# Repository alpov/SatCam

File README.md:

# PSAT-2 PSK/SSTV transponder

This repository hosts public parts of two boards from [PSAT2](http://www.aprs.org/psat2.html), a 1.5U CubeSat by US Naval Academy. These boards were developed at Dept. of Radio Electronics, Brno University of Technology, Czech Republic. The source files do not include authorization codes for SSTV and uplink commanding for PSK transponder.

**PSK transponder board** is an updated version of the PSK transponder with beacon and telemetry, used on [PSAT](http://www.aprs.org/psat.html) and [BRICSAT-1](http://www.aprs.org/bricsat-1.html). Transponder documentation available for [PSAT](http://www.urel.feec.vutbr.cz/esl/files/Projects/PSAT/P%20sat%20transponder%20WEB%20spec02.htm) and [BRICSAT-1](http://www.urel.feec.vutbr.cz/esl/files/Projects/BRICsat/Bricsat%20transponder%20WEB%20spec02.htm).

**SSTV transmitter board** provides a Slow-scan Television (SSTV) signal generator with PSK/CW telemetry, APRS uplink, and camera module. It is based on STM32F446RET6 microcontroller. Supported SSTV modes are Robot36, Robot72, MP73 and MP115.

## Important information (UPDATED Aug 2020)

* Current PSAT2 status
  * SSTV 70cm operational, images in Flash occasionally updated (thanks to PY5LF, OK2PNQ, OK5MP)
  * PSK 10m=>70cm transponder operational, mode A, open for users
  * APRS 2m is down (transmitter failure) => user SSTV commanding is not possible

* Please **send your SSTV images** to alpov@alpov.net. I am collecting the emails from reporters and occasionaly send them some news. Other info source is [AMSAT-BB](https://www.amsat.org/pipermail/amsat-bb/).
  * [Gallery of decoded SSTV images](http://www.urel.feec.vutbr.cz/esl/psat2/sstv/).
  * [Online telemetry decoder](http://www.urel.feec.vutbr.cz/esl/psat2/psat2tlm.php) - please use for PSK-31 telemetry upload.
  * [Decoded telemetry of PSK and SSTV boards](https://docs.google.com/spreadsheets/d/1X_4X0AgCshNDFIrDecOif41eRRwNzOKZwRn9tjI5_hs/edit?usp=sharing).
  * [SatNOGS for PSAT2](https://network.satnogs.org/observations/?future=0&good=1&bad=0&unvetted=0&failed=0&norad=44354).

* [Description of overlays](Docs/Overlay.md) in camera images.

* [Standalone camera design](Docs/SatCam.md) (for cancelled [PSAT3](http://www.aprs.org/psat3.html), [operations](Docs/PSAT3-operations.md)).

* [PocketQube camera design](Eagle/satcam_v4B_pocket_pcb_inside.pdf) (for [HADES](https://www.ure.es/camara-sstv-de-la-universidad-de-brno-para-el-satelite-hades-de-amsat-ea/) satellite).

## Transponder modes overview
The main function of the transponder is to receive PSK signals from 29.48 MHz uplink (passband from 29.4804 to 29.4826 MHz) and transmit them as a FM signal at 435.350 MHz downlink. The downlink is mixed with telemetry streams and SSTV images.

The PSK board switches between modes A to D according to available power. Battery voltage is checked periodically and after each transmitted character. If it crosses a boundary, the mode is switched. Moreover, if the voltage falls below a critical limit, the transmission is stopped immediately. This behavior can be observed in mode D, when only a part of the telemetry is transmitted.

All operations are limited to Sun detection, which is controlled by SUNWIRE signal. The SUNWIRE is fail-safe checked by state machine. After MCU reboot, the Sun signal is always high. It goes low after falling edge on SUNWIRE. If the SUNWIRE is low for more than 30 minutes, it is set to high automatically, otherwise with rising edge on SUNWIRE. Interconnects between both boards and PSAT-2 are shown [in a block diagram](Docs/psk_sstv_interconnect.png).

Communication is divided into 20sec time slots. There are 6 slots for modes A/B/C, and 9 slots for mode D. The telemetry is transmitted in every 1st slot or if PSK uplink is detected. Additionally, an SSTV image or telemetry is added to the transmitted signal. The time slots do not affect the PSK transponder function, so there is no need to fit with the PSK uplink signal into a time window. However, advanced functions such as commanding, telemetry and SSTV, are synchronized into these windows.

Users will be able to command these functions after the system has been successfully activated in space and we have completed successful checkout.

## Telemetry streams
The PSK MCU generates telemetry data in PSK31 format, which is transmitted on 435.350 MHz, carrier at 374 Hz. This telemetry consists of current and historical frame. Current frame contains frame counter, reboot counter, values of PSK level, AGC, battery voltage, 5V voltage, current, RX temperature, and several period counter values. History frame is pseudo-randomly selected from memory and contains the same information except for period counters. Example telemetry frame: *PSAT-2 C apng eFaaijtkpokoaB aaaa A aokF eEadjluappjxay*. Such frame can be [decoded with the provided PHP decoder](http://www.urel.feec.vutbr.cz/esl/psat2/psat2tlm.php). Valid telemetry frames are automatically saved for further analysis.

The other telemetry stream is generated by SSTV MCU, transmitted in PSK31 format on the same frequency, carrier at 280 Hz. Telemetry contains current state of non-persistent tick counter, measurements of MCU temperature and ambient light in lux, state of several counters (authorization, planned events, reboots, errors, audio starts, camera images, commands accepted, commands rejected, commands unauthorized). Example telemetry frame: *PSAT-2 S ashd aDbiaaaa qralaitkboFxaa*. Again, such frame can be [decoded with the provided PHP decoder](http://www.urel.feec.vutbr.cz/esl/psat2/psat2tlm.php).

## SSTV operation
SSTV MCU can be commanded through APRS commands. If no command is received during 60 seconds, it starts *auto* mode. In this mode, all transmissions are synchronized to PSK TX. SSTV board can transmit PSK telemetry or SSTV images in Robot36 and MP73 modes. Images are progressively selected alternately from ROM and FLASH. ROM images are hard-coded to firmware, while FLASH images are grabbed from on-board camera. After each reboot, first 8 images in FLASH are taken with 30sec separation.

APRS commands addressed to special callsign will change the mode to *manual*. Details on public commanding will be added after successful deployment and initial testing of the satellite.

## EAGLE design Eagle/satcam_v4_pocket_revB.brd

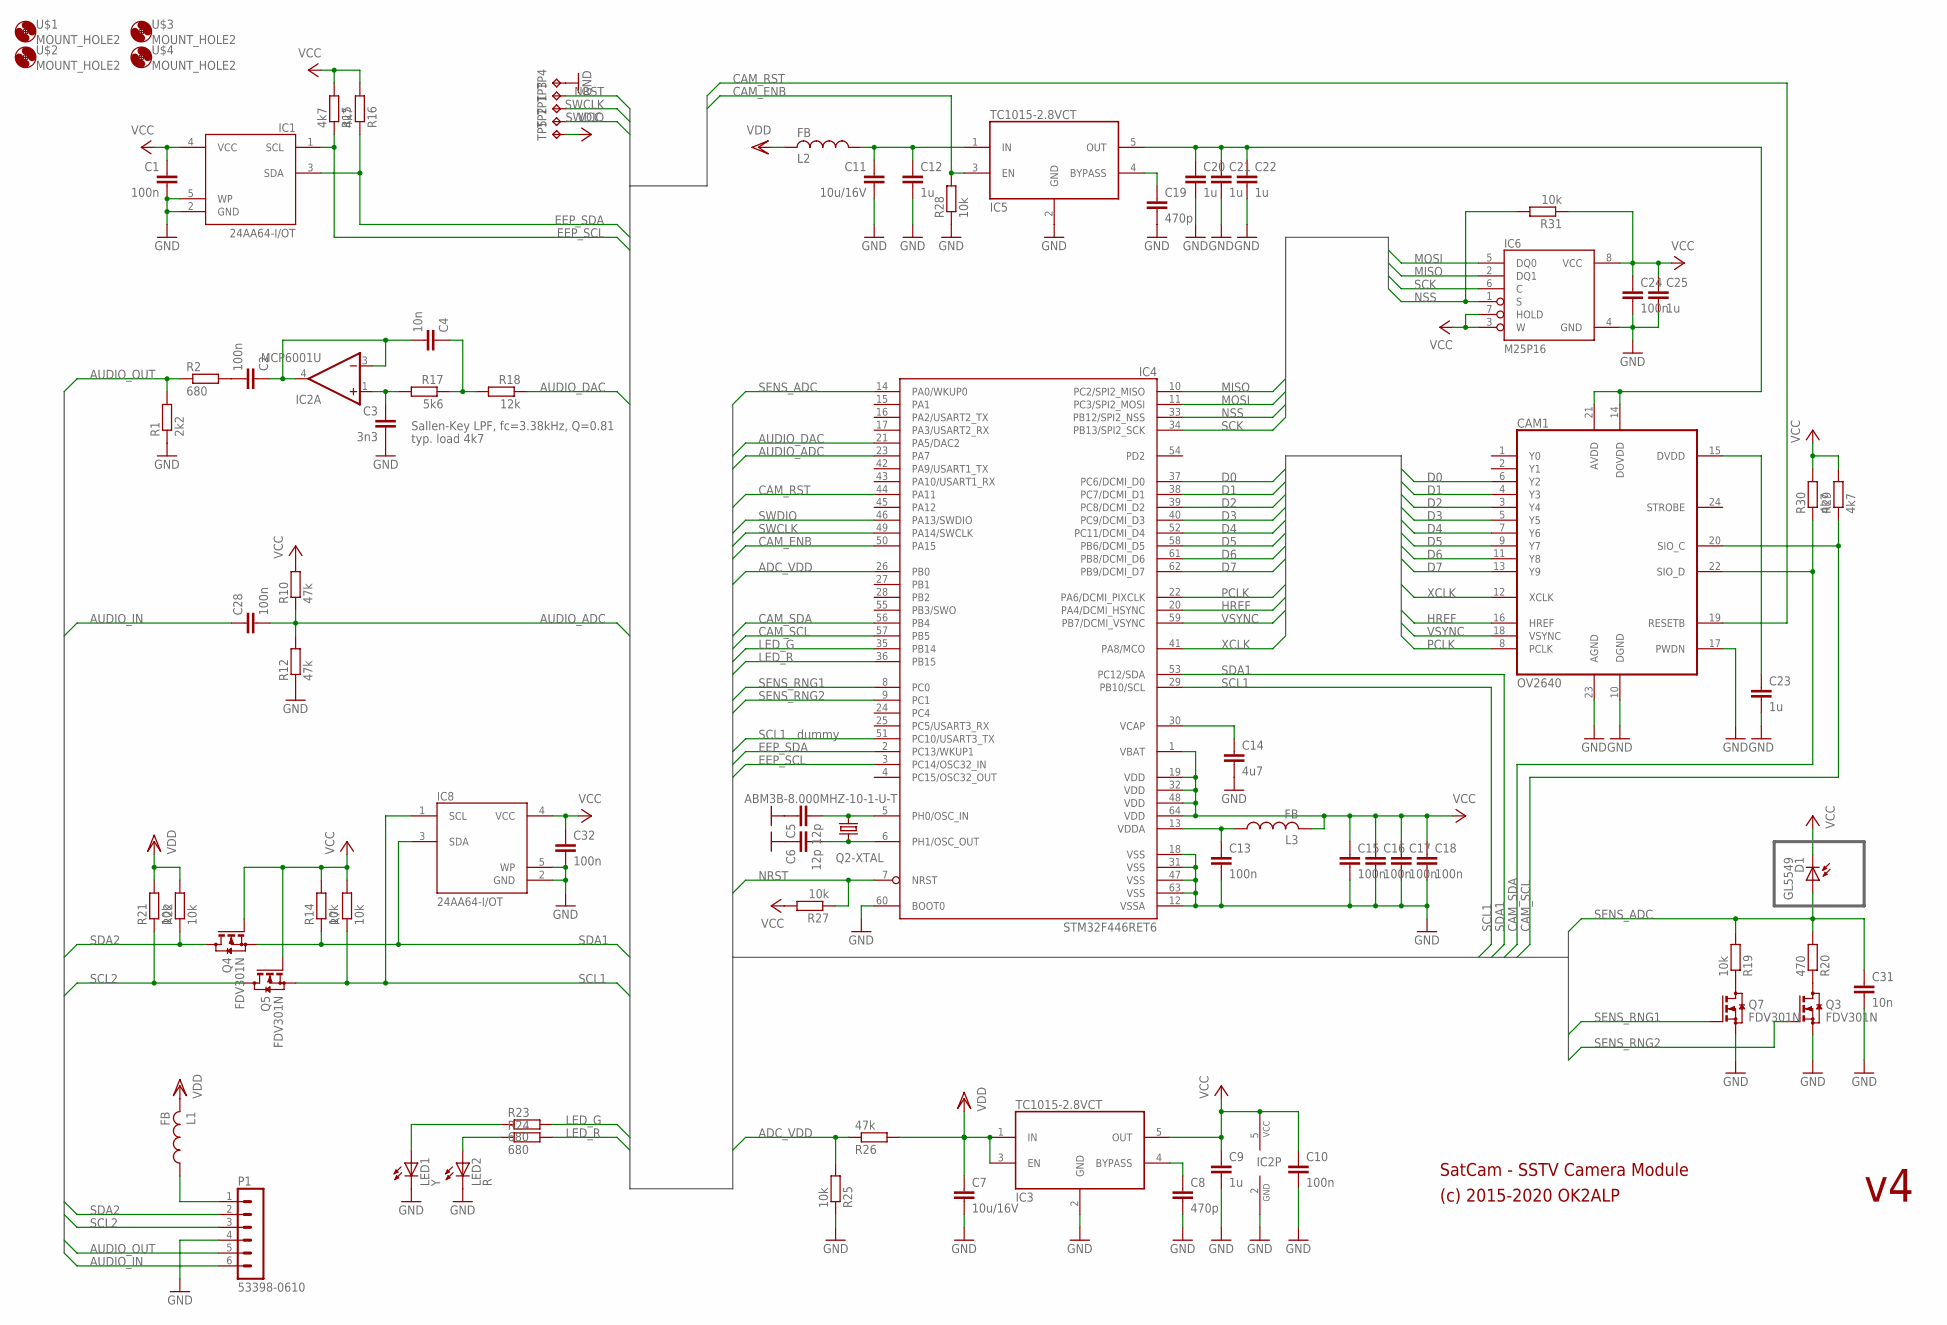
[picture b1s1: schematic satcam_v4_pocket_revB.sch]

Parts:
C1, C2, C10, C13, C15, C16, C17, C18, C24, C28, C32: 100n; C0603
C3: 3n3; C0603
C4, C31: 10n; C0603
C5, C6: 12p; C0603
C7, C11: 10u/16V; C0805K
C8, C19: 470p; C0603
C9, C12, C20, C25: 1u; C0603
C14: 4u7; C0603
C21, C22, C23: 1u; C0402
CAM1: OV2640; 52745-2490
D1: GL5549; LED3MM
IC1, IC8: 24AA64-I/OT; SOT23-5
IC2: MCP6001U; SOT23-5
IC3, IC5: TC1015-2.8VCT; SOT23-5
IC4: STM32F446RET6; TQFP64-10X10
IC6: M25P16; SO08
L1, L2, L3: FB; R0603
LED1: Y; CHIP-LED0603
LED2: R; CHIP-LED0603
P1: 53398-0610
Q2: ABM3B-8.000MHZ-10-1-U-T; CER5032
Q3, Q4, Q5, Q7: FDV301N; SOT23
R1: 2k2; R0603
R2, R23, R24: 680; R0603
R7, R14, R19, R21, R22, R25, R27, R28, R31: 10k; R0603
R10, R12, R26: 47k; R0603
R15, R16, R29, R30: 4k7; R0603
R17: 5k6; R0603
R18: 12k; R0603
R20: 470; R0603
TP1, TP2, TP3, TP4, TP5: TPB1,27; B1,27
U$1, U$2, U$3, U$4: MOUNT_HOLE2; 3,2

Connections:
ADC_VDD: IC4.26 (PB0), R25.2, R26.1
AUDIO_ADC: C28.2, IC4.23 (PA7), R10.1, R12.2
AUDIO_DAC: IC4.21 (PA5/DAC2), R18.1
AUDIO_IN: C28.1, P1.6
AUDIO_OUT: P1.5, R1.2, R2.1
CAM_ENB: IC4.50 (PA15), IC5.3 (EN), R28.2
CAM_RST: CAM1.19 (RESETB), IC4.44 (PA11)
CAM_SCL: CAM1.20 (SIO_C), IC4.57 (PB5), R29.1
CAM_SDA: CAM1.22 (SIO_D), IC4.56 (PB4), R30.1
D0: CAM1.6 (Y2), IC4.37 (PC6/DCMI_D0)
D1: CAM1.4 (Y3), IC4.38 (PC7/DCMI_D1)
D2: CAM1.3 (Y4), IC4.39 (PC8/DCMI_D2)
D3: CAM1.5 (Y5), IC4.40 (PC9/DCMI_D3)
D4: CAM1.7 (Y6), IC4.52 (PC11/DCMI_D4)
D5: CAM1.9 (Y7), IC4.58 (PB6/DCMI_D5)
D6: CAM1.11 (Y8), IC4.61 (PB8/DCMI_D6)
D7: CAM1.13 (Y9), IC4.62 (PB9/DCMI_D7)
EEP_SCL: IC1.1 (SCL), IC4.3 (PC14/OSC32_IN), R15.1
EEP_SDA: IC1.3 (SDA), IC4.2 (PC13/WKUP1), R16.1
GND: C1.2, C3.2, C5.1, C6.1, C7.2, C8.2, C9.2, C10.2, C11.2, C12.2, C13.2, C14.2, C15.2, C16.2, C17.2, C18.2, C19.2, C20.2, C21.2, C22.2, C23.2, C24.2, C25.2, C31.2, C32.2, CAM1.10 (DGND), CAM1.17 (PWDN), CAM1.23 (AGND), IC1.2 (GND), IC1.5 (WP), IC2.2 (GND), IC3.2 (GND), IC4.12 (VSSA), IC4.18 (VSS), IC4.31 (VSS), IC4.47 (VSS), IC4.60 (BOOT0), IC4.63 (VSS), IC5.2 (GND), IC6.4 (GND), IC8.2 (GND), IC8.5 (WP), LED1.C, LED2.C, P1.4, Q2.2 (GND), Q2.4 (GND), Q3.2 (S), Q7.2 (S), R1.1, R12.1, R25.1, R28.1, TP4.TP
HREF: CAM1.16 (HREF), IC4.20 (PA4/DCMI_HSYNC)
LED_G: IC4.35 (PB14), R23.2
LED_R: IC4.36 (PB15), R24.2
MISO: IC4.10 (PC2/SPI2_MISO), IC6.2 (DQ1)
MOSI: IC4.11 (PC3/SPI2_MOSI), IC6.5 (DQ0)
unnamed: C11.1, C12.1, IC5.1 (IN), L2.1
unnamed: C23.1, CAM1.15 (DVDD)
unnamed: C19.1, IC5.4 (BYPASS)
unnamed: L1.1, P1.1
unnamed: C8.1, IC3.4 (BYPASS)
unnamed: LED2.A, R24.1
unnamed: LED1.A, R23.1
unnamed: C14.1, IC4.30 (VCAP)
unnamed: Q7.3 (D), R19.1
unnamed: Q3.3 (D), R20.1
unnamed: C13.1, IC4.13 (VDDA), L3.1
unnamed: C6.2, IC4.6 (PH1/OSC_OUT), Q2.3 (2)
unnamed: C5.2, IC4.5 (PH0/OSC_IN), Q2.1
unnamed: C2.1, C4.2, IC2.3 (-IN), IC2.4 (OUT)
unnamed: C4.1, R17.1, R18.2
unnamed: C3.1, IC2.1 (+IN), R17.2
unnamed: C2.2, R2.2
NRST: IC4.7 (NRST), R27.1, TP3.TP
NSS: IC4.33 (PB12/SPI2_NSS), IC6.1 (S), R31.2
PCLK: CAM1.8 (PCLK), IC4.22 (PA6/DCMI_PIXCLK)
SCK: IC4.34 (PB13/SPI2_SCK), IC6.6 (C)
SCL1: IC4.29 (PB10/SCL), IC4.51 (PC10/USART3_TX), IC8.1 (SCL), Q5.2 (S), R7.1
SCL2: P1.3, Q5.3 (D), R21.1
SDA1: IC4.53 (PC12/SDA), IC8.3 (SDA), Q4.2 (S), R14.1
SDA2: P1.2, Q4.3 (D), R22.1
SENS_ADC: C31.1, D1.A, IC4.14 (PA0/WKUP0), R19.2, R20.2
SENS_RNG1: IC4.8 (PC0), Q7.1 (G)
SENS_RNG2: IC4.9 (PC1), Q3.1 (G)
SWCLK: IC4.49 (PA14/SWCLK), TP1.TP
SWDIO: IC4.46 (PA13/SWDIO), TP2.TP
VCAM: C20.1, C21.1, C22.1, CAM1.14 (DOVDD), CAM1.21 (AVDD), IC5.5 (OUT)
VCC: C1.1, C9.1, C10.1, C15.1, C16.1, C17.1, C18.1, C24.1, C25.1, C32.1, D1.K (C), IC1.4 (VCC), IC2.5 (VCC), IC3.5 (OUT), IC4.1 (VBAT), IC4.19 (VDD), IC4.32 (VDD), IC4.48 (VDD), IC4.64 (VDD), IC6.3 (W), IC6.7 (HOLD), IC6.8 (VCC), IC8.4 (VCC), L3.2, Q4.1 (G), Q5.1 (G), R7.2, R10.2, R14.2, R15.2, R16.2, R27.2, R29.2, R30.2, R31.1, TP5.TP
VDD: C7.1, IC3.1 (IN), IC3.3 (EN), L1.2, L2.2, R21.2, R22.2, R26.2
VSYNC: CAM1.18 (VSYNC), IC4.59 (PB7/DCMI_VSYNC)
XCLK: CAM1.12 (XCLK), IC4.41 (PA8/MCO)

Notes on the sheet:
typ. load 4k7
Sallen-Key LPF, fc=3.38kHz, Q=0.81
SatCam - SSTV Camera Module
(c) 2015-2020 OK2ALP
dummy

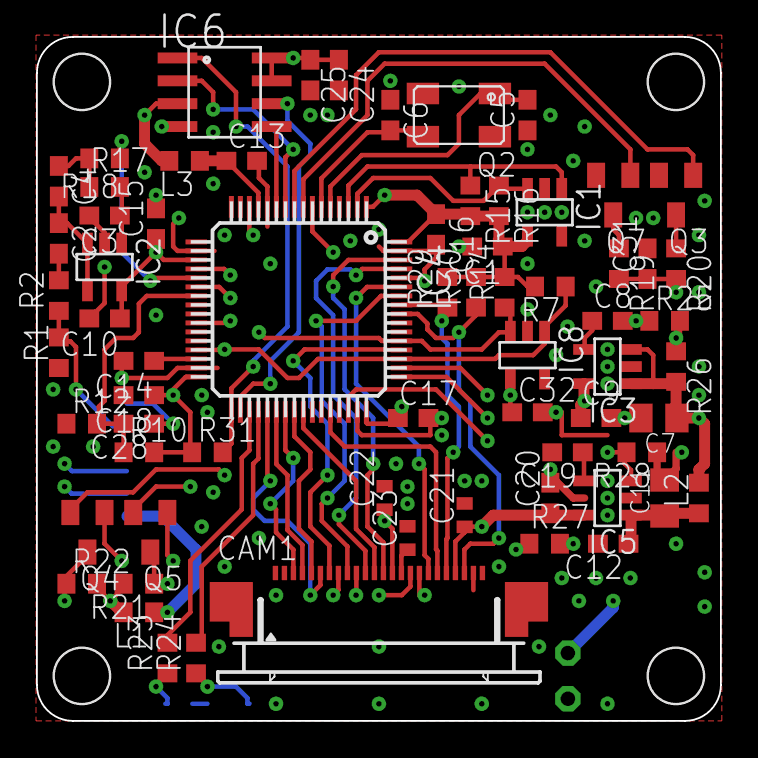
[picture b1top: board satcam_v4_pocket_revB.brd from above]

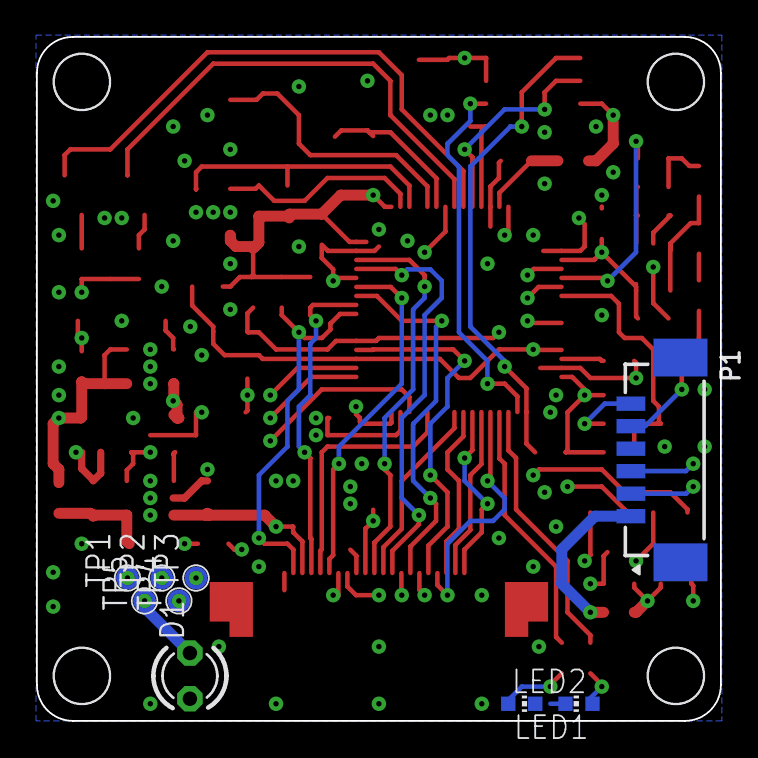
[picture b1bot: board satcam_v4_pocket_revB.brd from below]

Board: 4 copper layers, 38.0 x 38.0 mm, 80 parts (9 on the bottom side), 60 nets.

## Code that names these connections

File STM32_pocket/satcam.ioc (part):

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Mcu.Name=STM32F446R(C-E)Tx
Mcu.Package=LQFP64
Mcu.UserName=STM32F446RETx
PA0-WKUP.Signal=ADCx_IN0
PA11.GPIOParameters=GPIO_Label
PA11.GPIO_Label=CAM_RST
PA11.Signal=GPIO_Output
PA12.GPIOParameters=GPIO_Label
PA12.GPIO_Label=ADC1_IN8_dummy
PA12.Signal=GPIO_Analog
PA13.Mode=Trace_Asynchronous_SW
PA13.Signal=SYS_JTMS-SWDIO
PA14.Mode=Trace_Asynchronous_SW
PA14.Signal=SYS_JTCK-SWCLK
PA15.GPIOParameters=GPIO_Label
PA15.GPIO_Label=CAM_ENB
PA15.Signal=GPIO_Output
PA4.GPIOParameters=GPIO_Speed
PA4.GPIO_Speed=GPIO_SPEED_FREQ_VERY_HIGH
PA4.Mode=Slave_8_bits_External_Synchro
PA4.Signal=DCMI_HSYNC
PA5.Signal=COMP_DAC2_group
PA6.GPIOParameters=GPIO_Speed
PA6.GPIO_Speed=GPIO_SPEED_FREQ_VERY_HIGH
PA6.Mode=Slave_8_bits_External_Synchro
PA6.Signal=DCMI_PIXCLK
PA7.Signal=ADCx_IN7
PA8.GPIOParameters=GPIO_Label,GPIO_Speed
PA8.GPIO_Label=XCLK
PA8.GPIO_Speed=GPIO_SPEED_FREQ_VERY_HIGH
PA8.Signal=GPIO_Output
PB0.Signal=ADCx_IN8
PB10.Mode=I2C
PB10.Signal=I2C2_SCL
PB12.GPIOParameters=GPIO_Label,GPIO_Speed,PinState
PB12.GPIO_Label=SPI2_NSS
PB12.GPIO_Speed=GPIO_SPEED_FREQ_VERY_HIGH
PB12.PinState=GPIO_PIN_RESET
PB12.Signal=GPIO_Output
PB13.Mode=Full_Duplex_Master
PB13.Signal=SPI2_SCK
PB14.GPIOParameters=GPIO_Label
PB14.GPIO_Label=LED_G
PB14.Signal=GPIO_Output
PB15.GPIOParameters=GPIO_Label
PB15.GPIO_Label=LED_R
PB15.Signal=GPIO_Output
PB3.Mode=Trace_Asynchronous_SW
PB3.Signal=SYS_JTDO-SWO
PB4.GPIOParameters=GPIO_ModeDefaultOutputPP,GPIO_Label,PinState,GPIO_Speed,GPIO_PuPd
PB4.GPIO_Label=CAM_SDA
PB4.GPIO_ModeDefaultOutputPP=GPIO_MODE_OUTPUT_OD
PB4.GPIO_PuPd=GPIO_PULLUP
PB4.GPIO_Speed=GPIO_SPEED_FREQ_HIGH
PB4.PinState=GPIO_PIN_SET
PB4.Signal=GPIO_Output
PB5.GPIOParameters=GPIO_ModeDefaultOutputPP,GPIO_Label,PinState,GPIO_Speed,GPIO_PuPd
PB5.GPIO_Label=CAM_SCL
PB5.GPIO_ModeDefaultOutputPP=GPIO_MODE_OUTPUT_OD
PB5.GPIO_PuPd=GPIO_PULLUP
PB5.GPIO_Speed=GPIO_SPEED_FREQ_HIGH
PB5.PinState=GPIO_PIN_SET
PB5.Signal=GPIO_Output
PB6.GPIOParameters=GPIO_Speed
PB6.GPIO_Speed=GPIO_SPEED_FREQ_VERY_HIGH
PB6.Mode=Slave_8_bits_External_Synchro
PB6.Signal=DCMI_D5
PB7.GPIOParameters=GPIO_Speed
PB7.GPIO_Speed=GPIO_SPEED_FREQ_VERY_HIGH
PB7.Mode=Slave_8_bits_External_Synchro
PB7.Signal=DCMI_VSYNC
PB8.GPIOParameters=GPIO_Speed
PB8.GPIO_Speed=GPIO_SPEED_FREQ_VERY_HIGH
PB8.Mode=Slave_8_bits_External_Synchro
PB8.Signal=DCMI_D6
PB9.GPIOParameters=GPIO_Speed
PB9.GPIO_Speed=GPIO_SPEED_FREQ_VERY_HIGH
PB9.Mode=Slave_8_bits_External_Synchro
PB9.Signal=DCMI_D7
PC0.GPIOParameters=GPIO_Label
PC0.GPIO_Label=SENS_RNG1
PC0.Signal=GPIO_Output
PC1.GPIOParameters=GPIO_Label
PC1.GPIO_Label=SENS_RNG2
PC1.Signal=GPIO_Output
PC10.GPIOParameters=GPIO_Label
PC10.GPIO_Label=I2C2_SCL_dummy
PC10.Signal=GPIO_Analog
PC11.GPIOParameters=GPIO_Speed
PC11.GPIO_Speed=GPIO_SPEED_FREQ_VERY_HIGH
PC11.Mode=Slave_8_bits_External_Synchro
PC11.Signal=DCMI_D4
PC12.Mode=I2C
PC12.Signal=I2C2_SDA
PC13.GPIOParameters=GPIO_Label,GPIO_ModeDefaultOutputPP,PinState,GPIO_PuPd
PC13.GPIO_Label=EEP_SDA
PC13.GPIO_ModeDefaultOutputPP=GPIO_MODE_OUTPUT_OD
PC13.GPIO_PuPd=GPIO_PULLUP
PC13.PinState=GPIO_PIN_SET
PC13.Signal=GPIO_Output
PC14-OSC32_IN.GPIOParameters=GPIO_Label,GPIO_ModeDefaultOutputPP,PinState,GPIO_PuPd
PC14-OSC32_IN.GPIO_Label=EEP_SCL
PC14-OSC32_IN.GPIO_ModeDefaultOutputPP=GPIO_MODE_OUTPUT_OD
PC14-OSC32_IN.GPIO_PuPd=GPIO_PULLUP
PC14-OSC32_IN.PinState=GPIO_PIN_SET
PC14-OSC32_IN.Signal=GPIO_Output
PC2.Mode=Full_Duplex_Master
PC2.Signal=SPI2_MISO
PC3.Mode=Full_Duplex_Master
PC3.Signal=SPI2_MOSI
PC6.GPIOParameters=GPIO_Speed
PC6.GPIO_Speed=GPIO_SPEED_FREQ_VERY_HIGH
PC6.Mode=Slave_8_bits_External_Synchro
PC6.Signal=DCMI_D0
PC7.GPIOParameters=GPIO_Speed
PC7.GPIO_Speed=GPIO_SPEED_FREQ_VERY_HIGH
PC7.Mode=Slave_8_bits_External_Synchro
PC7.Signal=DCMI_D1
PC8.GPIOParameters=GPIO_Speed
PC8.GPIO_Speed=GPIO_SPEED_FREQ_VERY_HIGH
PC8.Mode=Slave_8_bits_External_Synchro
PC8.Signal=DCMI_D2
PC9.GPIOParameters=GPIO_Speed
PC9.GPIO_Speed=GPIO_SPEED_FREQ_VERY_HIGH
PC9.Mode=Slave_8_bits_External_Synchro
PC9.Signal=DCMI_D3
PH0-OSC_IN.Mode=HSE-External-Oscillator
PH0-OSC_IN.Signal=RCC_OSC_IN
PH1-OSC_OUT.Mode=HSE-External-Oscillator
PH1-OSC_OUT.Signal=RCC_OSC_OUT
RCC.HSE_VALUE=8000000
RCC.SYSCLKFreq_VALUE=8000000
RCC.SYSCLKSource=RCC_SYSCLKSOURCE_HSE
board=NUCLEO-F446RE
boardIOC=true

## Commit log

2017-01-31 SVN revision 984
2019-05-21 Added images
2019-05-21 SVN revision 1084
2019-09-16 SVN revision 1130
2019-10-23 SVN revision 1151
2019-10-23 SVN revision 1154
2019-10-23 SVN revision 1155
2019-10-24 SVN revision 1156
2019-11-01 SVN revision 1158
2019-11-13 SVN revision 1160
2019-11-27 SVN revision 1178
2020-01-27 SVN revision 1192
2020-08-24 SVN revision 1250
2020-08-24 SVN revision 1251
2020-09-02 SVN revision 1252
2022-06-10 SVN revision 1396

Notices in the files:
parts and their libraries:
con-molex-picoblade: Copyright (C) 2010, Bob Starr
